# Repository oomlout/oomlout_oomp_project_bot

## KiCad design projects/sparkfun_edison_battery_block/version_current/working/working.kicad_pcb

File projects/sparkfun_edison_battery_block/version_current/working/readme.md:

# Edison_Battery_Block by sparkfun  
This is a harvested standardized copy of a project from github.  
The original project can be found at:  
https://github.com/sparkfun/Edison_Battery_Block  
Please consult that link for additional, details, files, and license information.  
Note: It was auto harvested and if the original repo had more than one board file or anything out of the ordinary the files here are likely not representative.

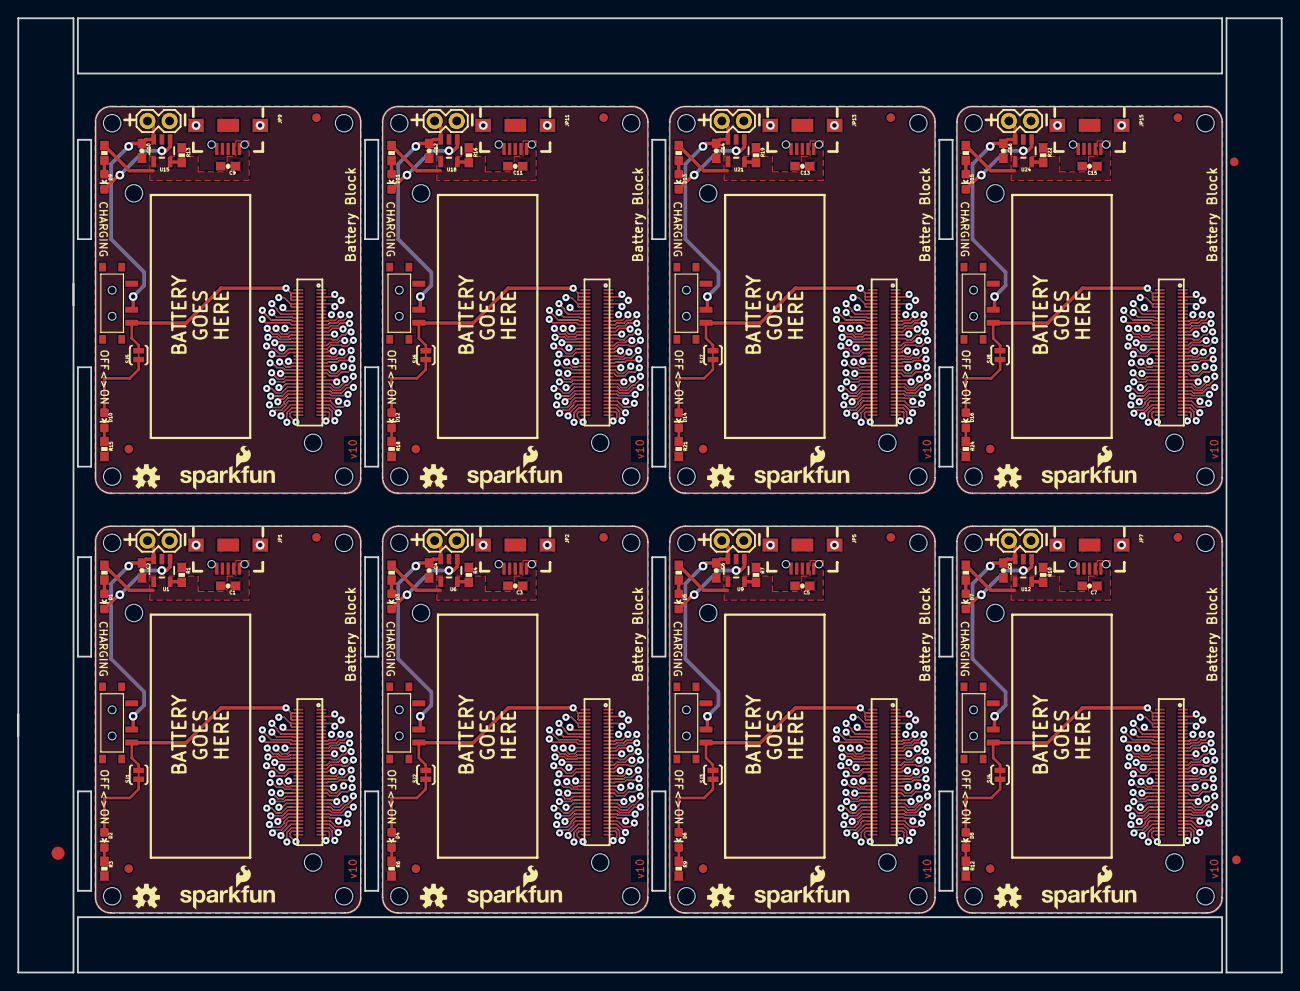
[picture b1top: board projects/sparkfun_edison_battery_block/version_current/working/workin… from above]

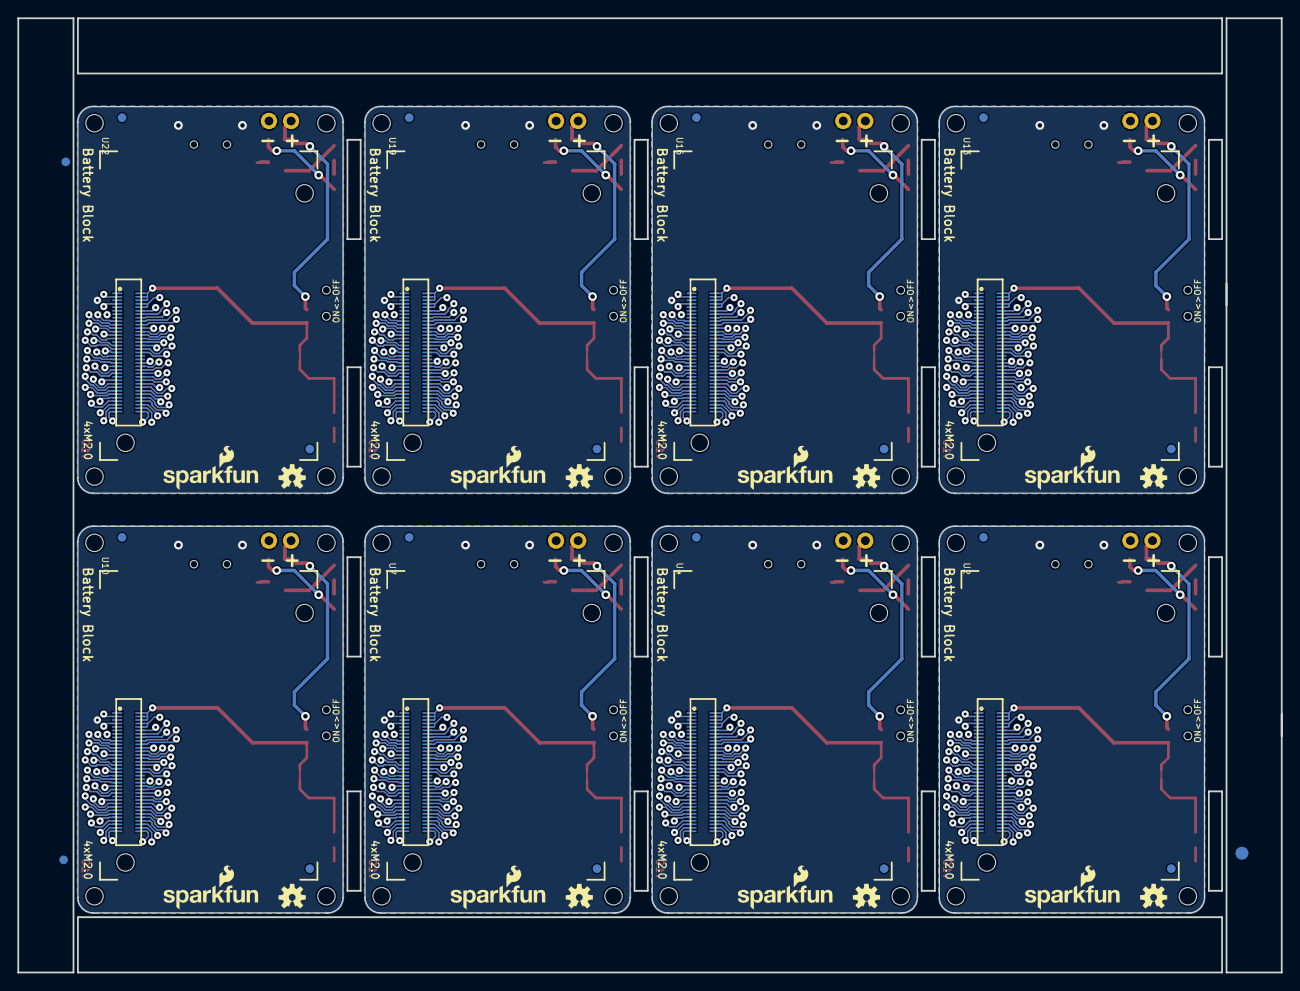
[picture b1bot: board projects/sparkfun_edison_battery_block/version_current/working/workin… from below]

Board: 4 copper layers, 145.3 x 109.7 mm, 214 parts (51 on the bottom side), 520 nets.

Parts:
@HOLE0, @HOLE1, @HOLE2, @HOLE3, @HOLE4, @HOLE5, @HOLE6, @HOLE7, @HOLE8, @HOLE9, @HOLE10, @HOLE11, @HOLE12, @HOLE13, @HOLE14, @HOLE15, @HOLE16, @HOLE17, @HOLE18, @HOLE19, @HOLE20, @HOLE21, @HOLE22, @HOLE23, @HOLE24, @HOLE25, @HOLE26, @HOLE27, @HOLE28, @HOLE29, @HOLE30, @HOLE31: (no value)
C1, C2, C3, C4, C5, C6, C7, C8, C9, C10, C11, C12, C13, C14, C15, C16: 4.7uF; 0603-CAP
D1, D3, D5, D7, D9, D11, D13, D15: RED; LED-0603
D2, D4, D6, D8, D10, D12, D14, D16: BLUE; LED-0603
E$1, E$2: FIDUCIAL-1.5X3
E$3, E$4, E$5, E$6: FIDUCIAL-1X2
FID1, FID2, FID3, FID4, FID5, FID6, FID7, FID8, FID9, FID10, FID11, FID12, FID13, FID14, FID15, FID16, FID17, FID18, FID19, FID20, FID21, FID22, FID23, FID24, FID25, FID26, FID27, FID28, FID29, FID30, FID31, FID32: FIDUCIAL1X2; FIDUCIAL-1X2
JP1, JP2, JP5, JP7, JP9, JP11, JP13, JP15: USB_MICROB_PLUG; USB-B-MICRO-SMD_V03
JP3, JP4, JP6, JP8, JP10, JP12, JP14, JP16: M02PTH; 1X02
LOGO1, LOGO2, LOGO5, LOGO7, LOGO9, LOGO11, LOGO13, LOGO15, LOGO17, LOGO19, LOGO21, LOGO23, LOGO25, LOGO27, LOGO29, LOGO31: OSHW-LOGOS; OSHW-LOGO-S
LOGO3, LOGO4, LOGO6, LOGO8, LOGO10, LOGO12, LOGO14, LOGO16, LOGO18, LOGO20, LOGO22, LOGO24, LOGO26, LOGO28, LOGO30, LOGO32: SFE_LOGO_NAME_FLAME.1_INCH; SFE_LOGO_NAME_FLAME_.1
R1, R4, R7, R10, R13, R16, R19, R22: 2.0k; 0603-RES
R2, R5, R8, R11, R14, R17, R20, R23: 330; 0603-RES
R3, R6, R9, R12, R15, R18, R21, R24: 1k; 0603-RES
SJ1, SJ2, SJ3, SJ4, SJ5, SJ6, SJ7, SJ8: LED DISABLE; PAD-JUMPER-2-NC_BY_TRACE_YES_SILK
SW1, SW2, SW3, SW4, SW5, SW6, SW7, SW8: SWITCH_SPDT; KPS-1290
U1, U6, U9, U12, U15, U18, U21, U24: MCP73831; SOT23-5
U2, U4, U7, U10, U13, U16, U19, U22: EDISON_CONNECTOR_FULLMOUNTING_HOLES; EDISON_DAUGHTER
U3, U5, U8, U11, U14, U17, U20, U23: EDISON_CONNECTOR_FULLHEADER; DF40C-70DP-0.4(51)

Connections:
1.8V: U2.12, U3.12
1.8V1: U4.12, U5.12
1.8V2: U7.12, U8.12
1.8V3: U10.12, U11.12
1.8V4: U13.12, U14.12
1.8V5: U16.12, U17.12
1.8V6: U19.12, U20.12
1.8V7: U22.12, U23.12
3.3V: U2.8, U2.10, U3.8, U3.10
3.3V1: U4.8, U4.10, U5.8, U5.10
3.3V2: U7.8, U7.10, U8.8, U8.10
3.3V3: U10.8, U10.10, U11.8, U11.10
3.3V4: U13.8, U13.10, U14.8, U14.10
3.3V5: U16.8, U16.10, U17.8, U17.10
3.3V6: U19.8, U19.10, U20.8, U20.10
3.3V7: U22.8, U22.10, U23.8, U23.10
DCIN: U2.14, U3.14
DCIN1: U4.14, U5.14
DCIN2: U7.14, U8.14
DCIN3: U10.14, U11.14
DCIN4: U13.14, U14.14
DCIN5: U16.14, U17.14
DCIN6: U19.14, U20.14
DCIN7: U22.14, U23.14
FAULT: U2.19, U3.19
FAULT1: U4.19, U5.19
FAULT2: U7.19, U8.19
FAULT3: U10.19, U11.19
FAULT4: U13.19, U14.19
FAULT5: U16.19, U17.19
FAULT6: U19.19, U20.19
FAULT7: U22.19, U23.19
FW_RCVR: U2.69, U3.69
FW_RCVR1: U4.69, U5.69
FW_RCVR2: U7.69, U8.69
FW_RCVR3: U10.69, U11.69
FW_RCVR4: U13.69, U14.69
FW_RCVR5: U16.69, U17.69
FW_RCVR6: U19.69, U20.69
FW_RCVR7: U22.69, U23.69
GND: C1.2, C2.2, JP1.GND1, JP1.SHIELD1, JP1.SHIELD2, JP1.SHIELD3, JP3.2, R1.1, R3.2, U1.2, U2.1, U2.5, U2.9, U2.11, U2.13, U2.15, U3.1, U3.5, U3.9, U3.11, U3.13, U3.15
GND1: C3.2, C4.2, JP2.GND1, JP2.SHIELD1, JP2.SHIELD2, JP2.SHIELD3, JP4.2, R4.1, R6.2, U4.1, U4.5, U4.9, U4.11, U4.13, U4.15, U5.1, U5.5, U5.9, U5.11, U5.13, U5.15, U6.2
GND2: C5.2, C6.2, JP5.GND1, JP5.SHIELD1, JP5.SHIELD2, JP5.SHIELD3, JP6.2, R7.1, R9.2, U7.1, U7.5, U7.9, U7.11, U7.13, U7.15, U8.1, U8.5, U8.9, U8.11, U8.13, U8.15, U9.2
GND3: C7.2, C8.2, JP7.GND1, JP7.SHIELD1, JP7.SHIELD2, JP7.SHIELD3, JP8.2, R10.1, R12.2, U10.1, U10.5, U10.9, U10.11, U10.13, U10.15, U11.1, U11.5, U11.9, U11.11, U11.13, U11.15, U12.2
GND4: C9.2, C10.2, JP9.GND1, JP9.SHIELD1, JP9.SHIELD2, JP9.SHIELD3, JP10.2, R13.1, R15.2, U13.1, U13.5, U13.9, U13.11, U13.13, U13.15, U14.1, U14.5, U14.9, U14.11, U14.13, U14.15, U15.2
GND5: C11.2, C12.2, JP11.GND1, JP11.SHIELD1, JP11.SHIELD2, JP11.SHIELD3, JP12.2, R16.1, R18.2, U16.1, U16.5, U16.9, U16.11, U16.13, U16.15, U17.1, U17.5, U17.9, U17.11, U17.13, U17.15, U18.2
GND6: C13.2, C14.2, JP13.GND1, JP13.SHIELD1, JP13.SHIELD2, JP13.SHIELD3, JP14.2, R19.1, R21.2, U19.1, U19.5, U19.9, U19.11, U19.13, U19.15, U20.1, U20.5, U20.9, U20.11, U20.13, U20.15, U21.2
GND7: C15.2, C16.2, JP15.GND1, JP15.SHIELD1, JP15.SHIELD2, JP15.SHIELD3, JP16.2, R22.1, R24.2, U22.1, U22.5, U22.9, U22.11, U22.13, U22.15, U23.1, U23.5, U23.9, U23.11, U23.13, U23.15, U24.2
GP1: U4.48, U5.48
GP2: U4.42, U5.42
GP3: U4.34, U5.34
GP4: U4.32, U5.32
GP5: U4.30, U5.30
GP6: U4.28, U5.28
GP7: U4.26, U5.26
GP8: U4.25, U5.25
GP9: U4.24, U5.24
GP10: U7.48, U8.48
GP11: U7.42, U8.42
GP12: U7.34, U8.34
GP12_PWM0: U2.35, U3.35
GP12_PWM1: U4.35, U5.35
GP12_PWM2: U7.35, U8.35
GP12_PWM3: U10.35, U11.35
GP12_PWM4: U13.35, U14.35
GP12_PWM5: U16.35, U17.35
GP12_PWM6: U19.35, U20.35
GP12_PWM7: U22.35, U23.35
GP13: U7.32, U8.32
GP13_PWM1: U2.33, U3.33
GP13_PWM2: U4.33, U5.33
GP13_PWM3: U7.33, U8.33
GP13_PWM4: U10.33, U11.33
GP13_PWM5: U13.33, U14.33
GP13_PWM6: U16.33, U17.33
GP13_PWM7: U19.33, U20.33
GP13_PWM8: U22.33, U23.33
GP14: U2.48, U3.48
GP15: U2.42, U3.42
GP16: U7.30, U8.30
GP17: U7.28, U8.28
GP18: U7.26, U8.26
GP19: U7.25, U8.25
GP19_I2C_1_SCL: U2.41, U3.41
GP19_I2C_1_SCL1: U4.41, U5.41
GP19_I2C_1_SCL2: U7.41, U8.41
GP19_I2C_1_SCL3: U10.41, U11.41
GP19_I2C_1_SCL4: U13.41, U14.41
GP19_I2C_1_SCL5: U16.41, U17.41
GP19_I2C_1_SCL6: U19.41, U20.41
GP19_I2C_1_SCL7: U22.41, U23.41
GP20: U7.24, U8.24
GP20_I2C_1_SDA: U2.43, U3.43
GP20_I2C_1_SDA1: U4.43, U5.43
GP20_I2C_1_SDA2: U7.43, U8.43
GP20_I2C_1_SDA3: U10.43, U11.43
GP20_I2C_1_SDA4: U13.43, U14.43
GP20_I2C_1_SDA5: U16.43, U17.43
GP20_I2C_1_SDA6: U19.43, U20.43
GP20_I2C_1_SDA7: U22.43, U23.43
GP21: U10.48, U11.48
GP22: U10.42, U11.42
GP23: U10.34, U11.34
GP24: U10.32, U11.32
GP25: U10.30, U11.30
GP26: U10.28, U11.28
GP27: U10.26, U11.26
GP27_I2C_6_SCL: U2.45, U3.45
GP27_I2C_6_SCL1: U4.45, U5.45
GP27_I2C_6_SCL2: U7.45, U8.45
GP27_I2C_6_SCL3: U10.45, U11.45
GP27_I2C_6_SCL4: U13.45, U14.45
GP27_I2C_6_SCL5: U16.45, U17.45
GP27_I2C_6_SCL6: U19.45, U20.45
GP27_I2C_6_SCL7: U22.45, U23.45
GP28: U10.25, U11.25
GP28_I2C_6_SDA: U2.47, U3.47
GP28_I2C_6_SDA1: U4.47, U5.47
GP28_I2C_6_SDA2: U7.47, U8.47
GP28_I2C_6_SDA3: U10.47, U11.47
GP28_I2C_6_SDA4: U13.47, U14.47
GP28_I2C_6_SDA5: U16.47, U17.47
GP28_I2C_6_SDA6: U19.47, U20.47
GP28_I2C_6_SDA7: U22.47, U23.47
GP29: U10.24, U11.24
GP30: U13.48, U14.48
GP31: U13.42, U14.42
GP32: U13.34, U14.34
GP33: U13.32, U14.32
GP34: U13.30, U14.30
GP35: U13.28, U14.28
GP36: U13.26, U14.26
GP37: U13.25, U14.25
GP38: U13.24, U14.24
GP39: U16.48, U17.48
GP40: U16.42, U17.42
GP40_I2S_2_CLK: U2.52, U3.52
GP40_I2S_2_CLK1: U4.52, U5.52
GP40_I2S_2_CLK2: U7.52, U8.52
GP40_I2S_2_CLK3: U10.52, U11.52
GP40_I2S_2_CLK4: U13.52, U14.52
GP40_I2S_2_CLK5: U16.52, U17.52
GP40_I2S_2_CLK6: U19.52, U20.52
GP40_I2S_2_CLK7: U22.52, U23.52
GP41: U16.34, U17.34
GP41_I2S_2_FS: U2.54, U3.54
GP41_I2S_2_FS1: U4.54, U5.54
GP41_I2S_2_FS2: U7.54, U8.54
GP41_I2S_2_FS3: U10.54, U11.54
GP41_I2S_2_FS4: U13.54, U14.54
GP41_I2S_2_FS5: U16.54, U17.54
GP41_I2S_2_FS6: U19.54, U20.54
GP41_I2S_2_FS7: U22.54, U23.54
GP42: U16.32, U17.32
GP42_I2S_2_RXD: U2.50, U3.50
GP42_I2S_2_RXD1: U4.50, U5.50
GP42_I2S_2_RXD2: U7.50, U8.50
GP42_I2S_2_RXD3: U10.50, U11.50
GP42_I2S_2_RXD4: U13.50, U14.50
GP42_I2S_2_RXD5: U16.50, U17.50
GP42_I2S_2_RXD6: U19.50, U20.50
GP42_I2S_2_RXD7: U22.50, U23.50
GP43: U16.30, U17.30
GP43_I2S_2_TXD: U2.56, U3.56
GP43_I2S_2_TXD1: U4.56, U5.56
GP43_I2S_2_TXD2: U7.56, U8.56
GP43_I2S_2_TXD3: U10.56, U11.56
GP43_I2S_2_TXD4: U13.56, U14.56
GP43_I2S_2_TXD5: U16.56, U17.56
GP43_I2S_2_TXD6: U19.56, U20.56
GP43_I2S_2_TXD7: U22.56, U23.56
GP44: U2.24, U3.24
GP45: U2.26, U3.26
GP46: U2.28, U3.28
GP47: U2.30, U3.30
GP48: U2.32, U3.32
GP49: U2.34, U3.34
GP50: U16.28, U17.28
GP51: U16.26, U17.26
GP52: U16.25, U17.25
GP53: U16.24, U17.24
GP54: U19.48, U20.48
GP55: U19.42, U20.42
GP56: U19.34, U20.34
GP57: U19.32, U20.32
GP58: U19.30, U20.30
GP59: U19.28, U20.28
GP60: U19.26, U20.26
GP61: U19.25, U20.25
GP62: U19.24, U20.24
GP63: U22.48, U23.48
GP64: U22.42, U23.42
GP65: U22.34, U23.34
GP66: U22.32, U23.32
GP67: U22.30, U23.30
GP68: U22.28, U23.28
GP69: U22.26, U23.26
GP70: U22.25, U23.25
GP71: U22.24, U23.24
GP77_SD_0_CD#: U2.60, U3.60
GP77_SD_0_CD#1: U4.60, U5.60
GP77_SD_0_CD#2: U7.60, U8.60
GP77_SD_0_CD#3: U10.60, U11.60
GP77_SD_0_CD#4: U13.60, U14.60
GP77_SD_0_CD#5: U16.60, U17.60
GP77_SD_0_CD#6: U19.60, U20.60
GP77_SD_0_CD#7: U22.60, U23.60
GP78_SD_0_CLK: U2.58, U3.58
GP78_SD_0_CLK1: U4.58, U5.58
GP78_SD_0_CLK2: U7.58, U8.58
GP78_SD_0_CLK3: U10.58, U11.58
GP78_SD_0_CLK4: U13.58, U14.58
GP78_SD_0_CLK5: U16.58, U17.58
GP78_SD_0_CLK6: U19.58, U20.58
GP78_SD_0_CLK7: U22.58, U23.58
GP79_SD_0_CMD: U2.62, U3.62
GP79_SD_0_CMD1: U4.62, U5.62
GP79_SD_0_CMD2: U7.62, U8.62
GP79_SD_0_CMD3: U10.62, U11.62
GP79_SD_0_CMD4: U13.62, U14.62
GP79_SD_0_CMD5: U16.62, U17.62
GP79_SD_0_CMD6: U19.62, U20.62
GP79_SD_0_CMD7: U22.62, U23.62
GP80_SD_0_DAT0: U2.66, U3.66
GP80_SD_0_DAT1: U4.66, U5.66
GP80_SD_0_DAT2: U7.66, U8.66
GP80_SD_0_DAT3: U10.66, U11.66
GP80_SD_0_DAT4: U13.66, U14.66
GP80_SD_0_DAT5: U16.66, U17.66
GP80_SD_0_DAT6: U19.66, U20.66
GP80_SD_0_DAT7: U22.66, U23.66
GP81_SD_0_DAT1: U2.70, U3.70
GP81_SD_0_DAT2: U4.70, U5.70
GP81_SD_0_DAT3: U7.70, U8.70
GP81_SD_0_DAT4: U10.70, U11.70
GP81_SD_0_DAT5: U13.70, U14.70
GP81_SD_0_DAT6: U16.70, U17.70
GP81_SD_0_DAT7: U19.70, U20.70
GP81_SD_0_DAT8: U22.70, U23.70
GP82_SD_0_DAT1: U4.64, U5.64
GP82_SD_0_DAT2: U2.64, U3.64
GP82_SD_0_DAT3: U7.64, U8.64
GP82_SD_0_DAT4: U10.64, U11.64
GP82_SD_0_DAT5: U13.64, U14.64
GP82_SD_0_DAT6: U16.64, U17.64
GP82_SD_0_DAT7: U19.64, U20.64
GP82_SD_0_DAT8: U22.64, U23.64
GP83_SD_0_DAT1: U4.68, U5.68
GP83_SD_0_DAT2: U7.68, U8.68
GP83_SD_0_DAT3: U2.68, U3.68
GP83_SD_0_DAT4: U10.68, U11.68
GP83_SD_0_DAT5: U13.68, U14.68
GP83_SD_0_DAT6: U16.68, U17.68
GP83_SD_0_DAT7: U19.68, U20.68
GP83_SD_0_DAT8: U22.68, U23.68
GP84_SD_CLK_FB: U2.44, U3.44
GP84_SD_CLK_FB1: U4.44, U5.44
GP84_SD_CLK_FB2: U7.44, U8.44
GP84_SD_CLK_FB3: U10.44, U11.44
GP84_SD_CLK_FB4: U13.44, U14.44
GP84_SD_CLK_FB5: U16.44, U17.44
GP84_SD_CLK_FB6: U19.44, U20.44
GP84_SD_CLK_FB7: U22.44, U23.44
GP109_SPI_2_CLK: U2.55, U3.55
GP109_SPI_2_CLK1: U4.55, U5.55
GP109_SPI_2_CLK2: U7.55, U8.55
GP109_SPI_2_CLK3: U10.55, U11.55
GP109_SPI_2_CLK4: U13.55, U14.55
GP109_SPI_2_CLK5: U16.55, U17.55
GP109_SPI_2_CLK6: U19.55, U20.55
GP109_SPI_2_CLK7: U22.55, U23.55
GP110_SPI_2_FS0: U2.53, U3.53
GP110_SPI_2_FS1: U4.53, U5.53
GP110_SPI_2_FS2: U7.53, U8.53
GP110_SPI_2_FS3: U10.53, U11.53
GP110_SPI_2_FS4: U13.53, U14.53
GP110_SPI_2_FS5: U16.53, U17.53
GP110_SPI_2_FS6: U19.53, U20.53
GP110_SPI_2_FS7: U22.53, U23.53
GP111_SPI_2_FS1: U2.51, U3.51
GP111_SPI_2_FS2: U4.51, U5.51
GP111_SPI_2_FS3: U7.51, U8.51
GP111_SPI_2_FS4: U10.51, U11.51
GP111_SPI_2_FS5: U13.51, U14.51
GP111_SPI_2_FS6: U16.51, U17.51
GP111_SPI_2_FS7: U19.51, U20.51
GP111_SPI_2_FS8: U22.51, U23.51
GP114_SPI_2_RXD: U2.59, U3.59
GP114_SPI_2_RXD1: U4.59, U5.59
GP114_SPI_2_RXD2: U7.59, U8.59
GP114_SPI_2_RXD3: U10.59, U11.59
GP114_SPI_2_RXD4: U13.59, U14.59
GP114_SPI_2_RXD5: U16.59, U17.59
GP114_SPI_2_RXD6: U19.59, U20.59
GP114_SPI_2_RXD7: U22.59, U23.59
GP115_SPI_2_TXD: U2.57, U3.57
GP115_SPI_2_TXD1: U4.57, U5.57
GP115_SPI_2_TXD2: U7.57, U8.57
GP115_SPI_2_TXD3: U10.57, U11.57
GP115_SPI_2_TXD4: U13.57, U14.57
GP115_SPI_2_TXD5: U16.57, U17.57
GP115_SPI_2_TXD6: U19.57, U20.57
GP115_SPI_2_TXD7: U22.57, U23.57
GP128_UART_1_CTS: U2.65, U3.65
GP128_UART_1_CTS1: U4.65, U5.65
GP128_UART_1_CTS2: U7.65, U8.65
GP128_UART_1_CTS3: U10.65, U11.65
GP128_UART_1_CTS4: U13.65, U14.65
GP128_UART_1_CTS5: U16.65, U17.65
GP128_UART_1_CTS6: U19.65, U20.65
GP128_UART_1_CTS7: U22.65, U23.65
GP129_UART_1_RTS: U2.63, U3.63
GP129_UART_1_RTS1: U4.63, U5.63
GP129_UART_1_RTS2: U7.63, U8.63
GP129_UART_1_RTS3: U10.63, U11.63
GP129_UART_1_RTS4: U13.63, U14.63
GP129_UART_1_RTS5: U16.63, U17.63
GP129_UART_1_RTS6: U19.63, U20.63
GP129_UART_1_RTS7: U22.63, U23.63
GP130_UART_1_RX: U2.61, U3.61
GP130_UART_1_RX1: U4.61, U5.61
GP130_UART_1_RX2: U7.61, U8.61
GP130_UART_1_RX3: U10.61, U11.61
GP130_UART_1_RX4: U13.61, U14.61
GP130_UART_1_RX5: U16.61, U17.61
GP130_UART_1_RX6: U19.61, U20.61
GP130_UART_1_RX7: U22.61, U23.61
GP131_UART_1_TX: U2.46, U3.46
GP131_UART_1_TX1: U4.46, U5.46
GP131_UART_1_TX2: U7.46, U8.46
GP131_UART_1_TX3: U10.46, U11.46
GP131_UART_1_TX4: U13.46, U14.46
GP131_UART_1_TX5: U16.46, U17.46
GP131_UART_1_TX6: U19.46, U20.46
GP131_UART_1_TX7: U22.46, U23.46
GP134_UART_2_RX: U2.22, U3.22
GP134_UART_2_RX1: U4.22, U5.22
GP134_UART_2_RX2: U7.22, U8.22
GP134_UART_2_RX3: U10.22, U11.22
GP134_UART_2_RX4: U13.22, U14.22
GP134_UART_2_RX5: U16.22, U17.22
GP134_UART_2_RX6: U19.22, U20.22
GP134_UART_2_RX7: U22.22, U23.22
GP135_UART_2_TX: U2.27, U3.27
GP135_UART_2_TX1: U4.27, U5.27
GP135_UART_2_TX2: U7.27, U8.27
GP135_UART_2_TX3: U10.27, U11.27
GP135_UART_2_TX4: U13.27, U14.27
GP135_UART_2_TX5: U16.27, U17.27
GP135_UART_2_TX6: U19.27, U20.27
GP135_UART_2_TX7: U22.27, U23.27
GP165: U2.25, U3.25
GP182_PWM1: U4.37, U5.37
GP182_PWM2: U2.37, U3.37
GP182_PWM3: U7.37, U8.37
GP182_PWM4: U10.37, U11.37
GP182_PWM5: U13.37, U14.37
GP182_PWM6: U16.37, U17.37
GP182_PWM7: U19.37, U20.37
GP182_PWM8: U22.37, U23.37
GP183_PWM1: U4.39, U5.39
GP183_PWM2: U7.39, U8.39
GP183_PWM3: U2.39, U3.39
GP183_PWM4: U10.39, U11.39
GP183_PWM5: U13.39, U14.39
GP183_PWM6: U16.39, U17.39
GP183_PWM7: U19.39, U20.39
GP183_PWM8: U22.39, U23.39
MSIC_SLP_CLK: U2.7, U3.7
MSIC_SLP_CLK1: U4.7, U5.7
MSIC_SLP_CLK2: U7.7, U8.7
MSIC_SLP_CLK3: U10.7, U11.7
MSIC_SLP_CLK4: U13.7, U14.7
MSIC_SLP_CLK5: U16.7, U17.7
MSIC_SLP_CLK6: U19.7, U20.7
MSIC_SLP_CLK7: U22.7, U23.7
unnamed: R4.2, U6.5
unnamed: D2.C, R3.1
unnamed: R1.2, U1.5
unnamed: D1.A, R2.1
unnamed: D1.C, U1.1
unnamed: D3.A, R5.1
unnamed: D2.A, SJ1.1
unnamed: D3.C, U6.1
unnamed: D4.C, R6.1
unnamed: D4.A, SJ2.1
unnamed: R7.2, U9.5
unnamed: D5.A, R8.1
unnamed: D5.C, U9.1
unnamed: D6.C, R9.1
unnamed: D6.A, SJ3.1
unnamed: R10.2, U12.5
unnamed: D7.A, R11.1
unnamed: D7.C, U12.1
unnamed: D8.C, R12.1
unnamed: D8.A, SJ4.1
unnamed: R13.2, U15.5
unnamed: D9.A, R14.1
unnamed: D9.C, U15.1
unnamed: D10.C, R15.1
unnamed: D10.A, SJ5.1
unnamed: R16.2, U18.5
unnamed: D11.A, R17.1
unnamed: D11.C, U18.1
unnamed: D12.C, R18.1
unnamed: D12.A, SJ6.1
unnamed: R19.2, U21.5
unnamed: D13.A, R20.1
unnamed: D13.C, U21.1
unnamed: D14.C, R21.1
unnamed: D14.A, SJ7.1
unnamed: R22.2, U24.5
unnamed: D15.A, R23.1
unnamed: D15.C, U24.1
unnamed: D16.C, R24.1
unnamed: D16.A, SJ8.1
OSC_CLK_OUT: U2.67, U3.67
OSC_CLK_OUT1: U4.67, U5.67
OSC_CLK_OUT2: U7.67, U8.67
OSC_CLK_OUT3: U10.67, U11.67
OSC_CLK_OUT4: U13.67, U14.67
OSC_CLK_OUT5: U16.67, U17.67
OSC_CLK_OUT6: U19.67, U20.67
OSC_CLK_OUT7: U22.67, U23.67
PSW: U2.21, U3.21
PSW1: U4.21, U5.21
PSW2: U7.21, U8.21
PSW3: U10.21, U11.21
PSW4: U13.21, U14.21
PSW5: U16.21, U17.21
PSW6: U19.21, U20.21
PSW7: U22.21, U23.21
PWRBTN#: U2.17, U3.17
PWRBTN#1: U4.17, U5.17
PWRBTN#2: U7.17, U8.17
PWRBTN#3: U10.17, U11.17
PWRBTN#4: U13.17, U14.17
PWRBTN#5: U16.17, U17.17
PWRBTN#6: U19.17, U20.17
PWRBTN#7: U22.17, U23.17
RCVR_MODE: U2.31, U3.31
RCVR_MODE1: U4.31, U5.31
RCVR_MODE2: U7.31, U8.31
RCVR_MODE3: U10.31, U11.31
RCVR_MODE4: U13.31, U14.31
RCVR_MODE5: U16.31, U17.31
RCVR_MODE6: U19.31, U20.31
RCVR_MODE7: U22.31, U23.31
RESET_OUT#: U2.36, U3.36
RESET_OUT#1: U4.36, U5.36
RESET_OUT#2: U7.36, U8.36
RESET_OUT#3: U10.36, U11.36
RESET_OUT#4: U13.36, U14.36
RESET_OUT#5: U16.36, U17.36
RESET_OUT#6: U19.36, U20.36
RESET_OUT#7: U22.36, U23.36
USB_DN: U2.18, U3.18
USB_DN1: U4.18, U5.18
USB_DN2: U7.18, U8.18
USB_DN3: U10.18, U11.18
USB_DN4: U13.18, U14.18
USB_DN5: U16.18, U17.18
USB_DN6: U19.18, U20.18
USB_DN7: U22.18, U23.18
USB_DP: U2.16, U3.16
USB_DP1: U4.16, U5.16
USB_DP2: U7.16, U8.16
USB_DP3: U10.16, U11.16
USB_DP4: U13.16, U14.16
USB_DP5: U16.16, U17.16
USB_DP6: U19.16, U20.16
USB_DP7: U22.16, U23.16
USB_ID: U2.3, U3.3
USB_ID1: U4.3, U5.3
USB_ID2: U7.3, U8.3
USB_ID3: U10.3, U11.3
USB_ID4: U13.3, U14.3
USB_ID5: U16.3, U17.3
USB_ID6: U19.3, U20.3
USB_ID7: U22.3, U23.3
USB_VBUS: U2.20, U3.20
USB_VBUS1: U4.20, U5.20
USB_VBUS2: U7.20, U8.20
USB_VBUS3: U10.20, U11.20
USB_VBUS4: U13.20, U14.20
USB_VBUS5: U16.20, U17.20
USB_VBUS6: U19.20, U20.20
USB_VBUS7: U22.20, U23.20
VBAT: C2.1, JP3.1, SW1.P, U1.3
VBAT1: C4.1, JP4.1, SW2.P, U6.3
VBAT2: C6.1, JP6.1, SW3.P, U9.3
VBAT3: C8.1, JP8.1, SW4.P, U12.3
VBAT4: C10.1, JP10.1, SW5.P, U15.3
VBAT5: C12.1, JP12.1, SW6.P, U18.3
VBAT6: C14.1, JP14.1, SW7.P, U21.3
VBAT7: C16.1, JP16.1, SW8.P, U24.3
VIN: C1.1, JP1.VBUS1, R2.2, U1.4
VIN1: C3.1, JP2.VBUS1, R5.2, U6.4
VIN2: C5.1, JP5.VBUS1, R8.2, U9.4
VIN3: C7.1, JP7.VBUS1, R11.2, U12.4
VIN4: C9.1, JP9.VBUS1, R14.2, U15.4
VIN5: C11.1, JP11.VBUS1, R17.2, U18.4
VIN6: C13.1, JP13.VBUS1, R20.2, U21.4
VIN7: C15.1, JP15.VBUS1, R23.2, U24.4
VSYS: SJ1.2, SW1.S, U2.2, U2.4, U2.6, U3.2, U3.4, U3.6
VSYS1: SJ2.2, SW2.S, U4.2, U4.4, U4.6, U5.2, U5.4, U5.6
VSYS2: SJ3.2, SW3.S, U7.2, U7.4, U7.6, U8.2, U8.4, U8.6
VSYS3: SJ4.2, SW4.S, U10.2, U10.4, U10.6, U11.2, U11.4, U11.6
VSYS4: SJ5.2, SW5.S, U13.2, U13.4, U13.6, U14.2, U14.4, U14.6
VSYS5: SJ6.2, SW6.S, U16.2, U16.4, U16.6, U17.2, U17.4, U17.6
VSYS6: SJ7.2, SW7.S, U19.2, U19.4, U19.6, U20.2, U20.4, U20.6
VSYS7: SJ8.2, SW8.S, U22.2, U22.4, U22.6, U23.2, U23.4, U23.6
V_BAT_BKUP: U2.23, U3.23
V_BAT_BKUP1: U4.23, U5.23
V_BAT_BKUP2: U7.23, U8.23
V_BAT_BKUP3: U10.23, U11.23
V_BAT_BKUP4: U13.23, U14.23
V_BAT_BKUP5: U16.23, U17.23
V_BAT_BKUP6: U19.23, U20.23
V_BAT_BKUP7: U22.23, U23.23

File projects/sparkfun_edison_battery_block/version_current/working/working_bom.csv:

"Id";"Designator";"Footprint";"Quantity";"Designation";"Supplier and ref";
1;"LOGO28,LOGO20,LOGO32,LOGO4,LOGO12,LOGO24,LOGO16,LOGO8,LOGO6,LOGO30,LOGO14,LOGO22,LOGO3,LOGO18,LOGO26,LOGO10";"SFE_LOGO_NAME_FLAME_.1";16;"SFE_LOGO_NAME_FLAME.1_INCH";;;
2;"R14,R2,R5,R8,R11,R17,R20,R23";"0603-RES";8;"330";;;
3;"C8,C6,C1,C7,C16,C13,C2,C11,C5,C15,C9,C4,C10,C3,C12,C14";"0603-CAP";16;"4.7uF";;;
4;"D8,D16,D4,D2,D14,D6,D12,D10";"LED-0603";8;"BLUE";;;
5;"R16,R1,R10,R19,R22,R4,R7,R13";"0603-RES";8;"2.0k";;;
6;"JP10,JP3,JP6,JP4,JP16,JP14,JP8,JP12";"1X02";8;"M02PTH";;;
7;"@HOLE7,@HOLE30,@HOLE31,@HOLE13,@HOLE2,@HOLE5,@HOLE6,@HOLE14,@HOLE0,@HOLE4,@HOLE28,@HOLE15,@HOLE29,@HOLE23,@HOLE1,@HOLE9,@HOLE26,@HOLE18,@HOLE22,@HOLE12,@HOLE16,@HOLE27,@HOLE19,@HOLE11,@HOLE17,@HOLE24,@HOLE3,@HOLE25,@HOLE20,@HOLE21,@HOLE10,@HOLE8";"";32;"";;;
8;"FID21,FID17,FID18,FID9,FID25,FID22,FID10,FID6,FID5,FID14,FID1,FID29,FID2,FID13,FID26,FID30,FID19,FID23,FID8,FID12,FID16,FID3,FID27,FID4,FID24,FID32,FID31,FID11,FID15,FID20,FID7,FID28";"FIDUCIAL-1X2";32;"FIDUCIAL1X2";;;
9;"SJ8,SJ5,SJ2,SJ7,SJ4,SJ3,SJ1,SJ6";"PAD-JUMPER-2-NC_BY_TRACE_YES_SILK";8;"LED DISABLE";;;
10;"U9,U12,U1,U15,U6,U24,U18,U21";"SOT23-5";8;"MCP73831";;;
11;"SW6,SW5,SW1,SW7,SW8,SW3,SW2,SW4";"KPS-1290";8;"SWITCH_SPDT";;;
12;"LOGO1,LOGO31,LOGO15,LOGO19,LOGO23,LOGO11,LOGO7,LOGO27,LOGO9,LOGO21,LOGO17,LOGO2,LOGO25,LOGO13,LOGO5,LOGO29";"OSHW-LOGO-S";16;"OSHW-LOGOS";;;
13;"JP9,JP13,JP15,JP7,JP5,JP1,JP2,JP11";"USB-B-MICRO-SMD_V03";8;"USB_MICROB_PLUG";;;
14;"R12,R21,R6,R15,R3,R18,R9,R24";"0603-RES";8;"1k";;;
15;"E$4,E$5,E$3,E$6";"FIDUCIAL-1X2";4;"";;;
16;"D1,D5,D11,D7,D3,D9,D13,D15";"LED-0603";8;"RED";;;
17;"E$1,E$2";"FIDUCIAL-1.5X3";2;"";;;
18;"U23,U3,U17,U20,U5,U8,U11,U14";"DF40C-70DP-0.4(51)";8;"EDISON_CONNECTOR_FULLHEADER";;;
19;"U2,U16,U13,U4,U19,U10,U7,U22";"EDISON_DAUGHTER";8;"EDISON_CONNECTOR_FULLMOUNTING_HOLES";;;
